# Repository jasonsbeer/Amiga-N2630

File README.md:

The N2630 is a 50MHz Motorolla MC68030 CPU card with additional RAM and ATA device port for the Amiga 2000 family of computers. It is installed in the CPU slot where it immediately upgrades the system to the MC68030 processor with FPU, up to 264 megabytes of Fast RAM, and an ATA port. The N2630 is intended to be an evolution of the A2630 card.  

<br />Look for the N2630 channel on Discord: https://discord.gg/NU7SPYfNFj  

## CURRENT STATUS:
**Revision 4.1.0a/b is the current production release.**  

Sub-revision "a" supports the PLCC footprint MC68882. Sub-revision "b" supports the PGA footprint MC68882. They are otherwise identical.  

See the [issues](https://github.com/jasonsbeer/Amiga-N2630/issues) tab for known issues. [Click here](/TestedDevices.md) to see a list of devices tested with the N2630.

## Features
1. Motorola 68030 microprocessor running at 50MHz.
2. Motorola 68882 math coprocessor running up to 50MHz.
3. 4 or 8 megabytes of Zorro 2 Fast RAM.
4. 16 to 256 megabytes of Zorro 3 Fast RAM.
5. ATA port with 40-pin cable and compact flash card options.

## Assembly Notes
Click [here](/AssemblyNotes.md) for more information on building the N2630.

## Installation Notes
This card may be installed in any Amiga 2000 computer. Installation is simply inserting the card into the 86 pin CPU/Coprocessor slot of the Amiga computer. There are no software drivers to install.  Kickstart v37.300 and greater is recommended.

**IMPORTANT:** Before installing a Revision 4.x.x or greater N2630, it is necessary to determine if you have an early, non-cost reduced motherboard. If your motherboard is marked "Made In Germany" and "(C) 1986 Commodore" on the left side of the board, you have a non-cost reduced Amiga 2000 board, designated "A2000" in this documentation. An example of a non-cost reduced Amiga 2000 motherboard can be see [here](http://amiga.resource.cx/photos/a2000,1). In the event you have an non-cost reduced "A2000" motherboard, you must remove the Motorola 68000 processor from the Amiga 2000 motherboard and place a jumper at J302 of the N2630.  All other Amiga 2000 motherboards are designated "B2000" and should leave the Motorola 68000 in place. Revision 3.0.x cards do not support the original German A2000. 

**NOTES:**  
**1) Hardware revision 4.x.x supports the original Germal A2000, but is untested.**  
**2) The A2091 hard drive card will not operate correctly when using Kickstart 1.x on a revision 6.2 or newer Amiga 2000 with the N2630 or A2630 CPU cards. You must use Kickstart 2.04 or newer.**

## 68030 Mode
By default, the N2630 starts in 68030 mode. When in 68030 mode, all installed RAM and the ATA device port are active.

## 68000 Mode
When desired, the 68030 may be disabled during a cold or warm start. This results in the Amiga falling back to the 68000 processor. This may be desired when software does not run correctly on the 68030 processor. To start up in 68000 mode, hold down the right mouse button during startup. Select "68000" and the Amiga will reset with the 68000 as the active processor. When in 68000 mode, the ATA port and on-board RAM are inactive. Motorola 68000 mode is not available with A2000 motherboards.

## 68882 Math Coprocessor (FPU)
The Motorolla MC68882 (or MC68881) floating point unit may be optionally added to the N2630. The FPU is typically driven at the same clock frequency as the MC68030 via the X1 oscillator, but may be clocked independently via the X2 oscillator (see Table 3, J202).

## ROMs
The N2630 requires two 27C256 EPROMs (burned by the user) to function. The ROMs handle the system startup for CPU selection and contains the [LIDE.device](https://github.com/LIV2/lide.device) AUTOBOOT ROM. See the instructions [here](/ROMs.md) for burning the N2630 ROMs.

## FAST RAM
The N2630 uses SDRAM to provide the necessary memory for the Amiga system. SDRAM is the successor to Fast Page Memory found in devices such as the Amiga 3000, A2630 processor card, and other computers of the time. SDRAMs are a cost effective way to supply memory to older systems and are readily available either new or from unused memory modules. 

### Zorro 2
Zorro 2 RAM is the Amiga RAM found in the 24 bit address space of the Motorola MC68000 processor. The Zorro 2 RAM on the N2630 is accessed by the 68030 as a 32-bit data bus and supports 16-bit DMA activities of the Zorro 2 bus. Placing a jumper at position J404 will limit the amount of RAM to 4MB in the Zorro 2 space, allowing 4MB of address space to be made available to other Zorro 2 devices. As an example, if you have a 4MB Zorro 2 video card, it will be necessary to set jumper J404 to free up this address space for the video card. Failure to do so will result in the video card failing to pass the AUTOCONFIG process. As another example, if you have two 4MB Zorro 2 devices, such as a video card and Bridge card, these devices require the entire 8MB Zorro 2 address space. In this situation, you must disable the Zorro 2 RAM entirely by placing a jumper at J403.

Using expansion memory on the Zorro 2 bus is not recommended, as this will negatively impact the performance of the MC68030 when accessing this memory on the Zorro 2 bus. The expansion memory on the N2630 should always be used as a first choice.

NOTE: Any SDRAM at least 2Mx16 in capacity in the 54-TSOP II footprint may be placed. However, it is not possible to achieve more than 8 megabytes of Zorro 2 RAM capacity. 

### Zorro 3
Zorro 3 RAM is the Amiga RAM found in the 32-bit address space of the Motorola MC68030 processor. The Zorro 3 RAM on the N2630 supports the cache burst mode of the 68030 processor. Both Zorro 2 and Zorro 3 RAM are used together on the N2630 card. Thus, the total memory available to the system will be the sum of the Zorro 2 and Zorro 3 RAM. 

Zorro 3 SDRAMs may be installed in different configurations to achieve a specific amount of final RAM (Table 1a). SDRAM must be installed in pairs, or banks, to achieve the needed 32 bit data path. Positions U406 and U407 represent the "low" bank and positions U408 and U409 represent the "high" bank. The banks must be populated as the low bank only or both low and high banks. The high bank will not function without the low bank populated. The SDRAM footprint is 54-TSOP II. The indicated jumpers must be set as shown or your system may not function correctly. When installing both banks, jumpers J400 and J401 must be set as shown in tables 1b and 1c. If only the low bank is populated, these jumpers are not used.

The Zorro 3 memory supports AUTOCONFIG with Kickstart 2.04 and newer and will be auto sized by Amiga OS. When using Kickstart version 1.x, place a jumper at J405 to disable the Zorro 3 AUTOCONFIG. An addmem style program may be used to add the Zorro 3 memory to the Amiga's memory pool. See Table 1d for the N2630 Zorro 3 memory map.

**Table 1a.** Possible Zorro 3 RAM Combinations for the N2630.
Desired Zorro</br>3 RAM (MB)|SDRAM|Low Bank</br>(U406 and U407)|High Bank</br>(U408 and U409)
-|-|-|-
16|4MX16|Populated<sup>A</sup>|Unpopulated<sup>B</sup>
32|4MX16|Populated|Populated
32|8MX16|Populated|Unpopulated
64|8MX16|Populated|Populated
64|16MX16|Populated|Unpopulated
128|16Mx16|Populated|Populated
128|32MX16|Populated|Unpopulated
256|32MX16|Populated|Populated

<sup>A</sup>These SDRAM positions are populated by the SDRAM indicated.  
<sup>B</sup>This SDRAM positions are not populated.

**Table 1b.** SDRAM Bank Jumper Setting.
Zorro 3 RAM</br>Banks Populated|J400
-|-
Low Bank Only|Open<sup>A</sup>
Both Banks|Shorted<sup>B</sup>

<sup>A</sup>No jumper.  
<sup>B</sup>Jumper placed. 
  
**Table 1c.** Jumper Configurations When Both Low and High Memory Banks Are Populated.
Desired Zorro</br>3 RAM (MB)|SDRAM</br>Capacity|J401<sup>[A]</sup>|J402<sup>[A]</sup>
-|-|-|-
32|4MX16|Open<sup>[B]</sup>|Shorted<sup>[C]</sup>
64|8MX16|Shorted|Open
128|16Mx16|Shorted|Shorted
256|32MX16|Open|Open

<sup>A</sup>Ignored when J400 is open.  
<sup>B</sup>No jumper.  
<sup>C</sup>Jumper placed.  

**Table 1d.** N2630 Zorro 3 Memory Map.
Desired Zorro</br>3 RAM (MB)|Starting Address|Ending Address
-|-|-
16|$40000000|$40FFFFFF
32|$40000000|$41FFFFFF
64|$40000000|$43FFFFFF
128|$40000000|$47FFFFFF
256|$40000000|$4FFFFFFF

## ATA Port
The N2630 includes a buffered, host terminated AUTOBOOT ATA port for hard drives and ATAPI devices. The N2630 implements [LIDE.device](https://github.com/LIV2/lide.device) as the ATA driver. The driver must be present on the N2630 ROMs for the ATA port to function. See [ROMs](#roms) for more details. The ATA port may be accessed via the 40-pin ATA header and the compact flash card slot. There are a few different ways to combine devices on the port, but the total number of ATA devices on the N2630 cannot exceed two (master and slave). For instructions on installing a new hard drive on Amiga computers, refer to the [Commodore Hard Drive User's Guide](DataSheet/Hard_Drive_Users_Guide.pdf). This includes the HDToolBox user guide and other useful information for setting up both ATA and SCSI devices. 

The ATA logic supports four speed modes: PIO0, PIO2, PIO4, and SanDisk Ultra 2 (see Table 2B). The modes PIO0, PIO2, and PIO4 follow the published timing specifications of those modes, with PIO0 being the slowest. The SanDisk Ultra 2 mode was developed for the SanDisk Ultra 2 compact flash card and is capable of 7.4M/s transfer rate. The SanDisk Ultra 2 mode is an undocumented ATA timing and may or may not work with other devices. The speed mode you select will be determined by the slowest ATA device on your system. To determine what speed your devices support, it is recommended to start with the slowest setting (PIO0) and adjust one setting faster until one of your devices stops working. The mode you choose should be the fastest mode where all devices function correctly. Jumpers should only be changed while the system is off.

Each ATA device must be set as slave or master. Devices present on the 40 pin ATA port may use cable select by shorting J905 when using a proper cable select ATA cable. See the manual for each device on how to designate the device's master or slave setting. Master and slave for the compact flash device are set via J901 on the N2630.

**NOTE:** The compact flash card slot is not affected by the cable select jumper (J905).  Thus, J905 should only be used when a proper cable select ATA cable is implemented on the 40 pin ATA port.

**Table 2A.** ATA Configuration Jumper Settings.
Jumper|Description|Open<sup>[A]</sup>|Shorted<sup>[B]</sup>
-|-|-|-
J900|RESERVED||
J901|Compact Flash Select|Slave|Master
J902|PIO MODE||
J903|PIO MODE||
J904|RESERVED||
J905|Cable Select|Disable|Enable

<sup>A</sup>No jumper.  
<sup>B</sup>Jumper placed. 

**Table 2B.** ATA PIO Mode.
Mode|J902|J903
-|-|-
PIO0|Shorted<sup>[A]</sup>|Shorted|
PIO2|Shorted|Open<sup>[B]</sup>|
PIO4|Open|Shorted|
SanDisk Ultra 2|Open|Open|

<sup>A</sup>Jumper placed.  
<sup>B</sup>No jumper.  

## Other Jumper Settings
In the following tables, OPEN indicates no jumper. Shorted indicates the presence of a jumper on the pins indicated. All jumpers must be set correctly or you may encounter unexpected behaviors or failure to boot.

**Table 3a.** Configuration Jumper Settings
Jumper|Description|Shorted|Open<sup>[A]</sup>
-|-|-|-
J302|Amiga Version|A2000|B2000
J304|OS Mode|Unix|Amiga OS
J403|Zorro 2 RAM|Disable|Enable
J404|Z2 4/8MB|4MB|8MB
J405|Zorro 3 RAM|Disable|Enable

<sup>A</sup>The factory configuration for all jumpers is open (no jumper).  

**Table 3b.** System Clock Jumper Settings
Jumper|Description|1-2|2-3
-|-|-|-
J202|FPU Clock|X1<sup>[A]</sup>|X2<sup>[B]</sup>

<sup>A</sup>FPU clock from X1. Factory default.  
<sup>B</sup>FPU clock from X2.

## Revision History
<strong>Revision 4.1.0a/b</strong>  
   Added ATA activity light buffer to address config issues with some ATA devices.  
   Changed polarity of the ATA LED header.  
   
<strong>Revision 4.0.1a/b</strong>  
   Sub-revision 'a' supports PLCC MC68882, sub-revision 'b' supports the PGA MC68882.  
   Changed jumper footprint to increase ease of assembly.  
   Added order number location for JLCPCB.  
   Added support for original German A2000 machines.
   
<strong>Revision 3.0.1</strong>  
   Added copper thieving areas to top and bottom layers.  
   
<strong>Revision 3.0</strong>  
   Initial production release.  

## Acknowledgements
Dave Haynie for sharing the A2630 technical details with the Amiga community.  
Matt Harlum (LIV2) for sharing his Gayle ATA code, LIDE.device, submitting code improvements, listening my struggles, and his numerous other contributions to this project.  
Stephen Durham (steveed) for loaning me his ethernet cards.  
Members of the Discord testing group: LIV2, steeveed, Chrissy, Pillock.  
Everyone who made the Amiga possible.  

Last Updated: March 26, 2024

## License
<br />This work is licensed under a <a rel="license" href="http://creativecommons.org/licenses/by-nc-sa/4.0/">Creative Commons Attribution-NonCommercial-ShareAlike 4.0 International License</a>.

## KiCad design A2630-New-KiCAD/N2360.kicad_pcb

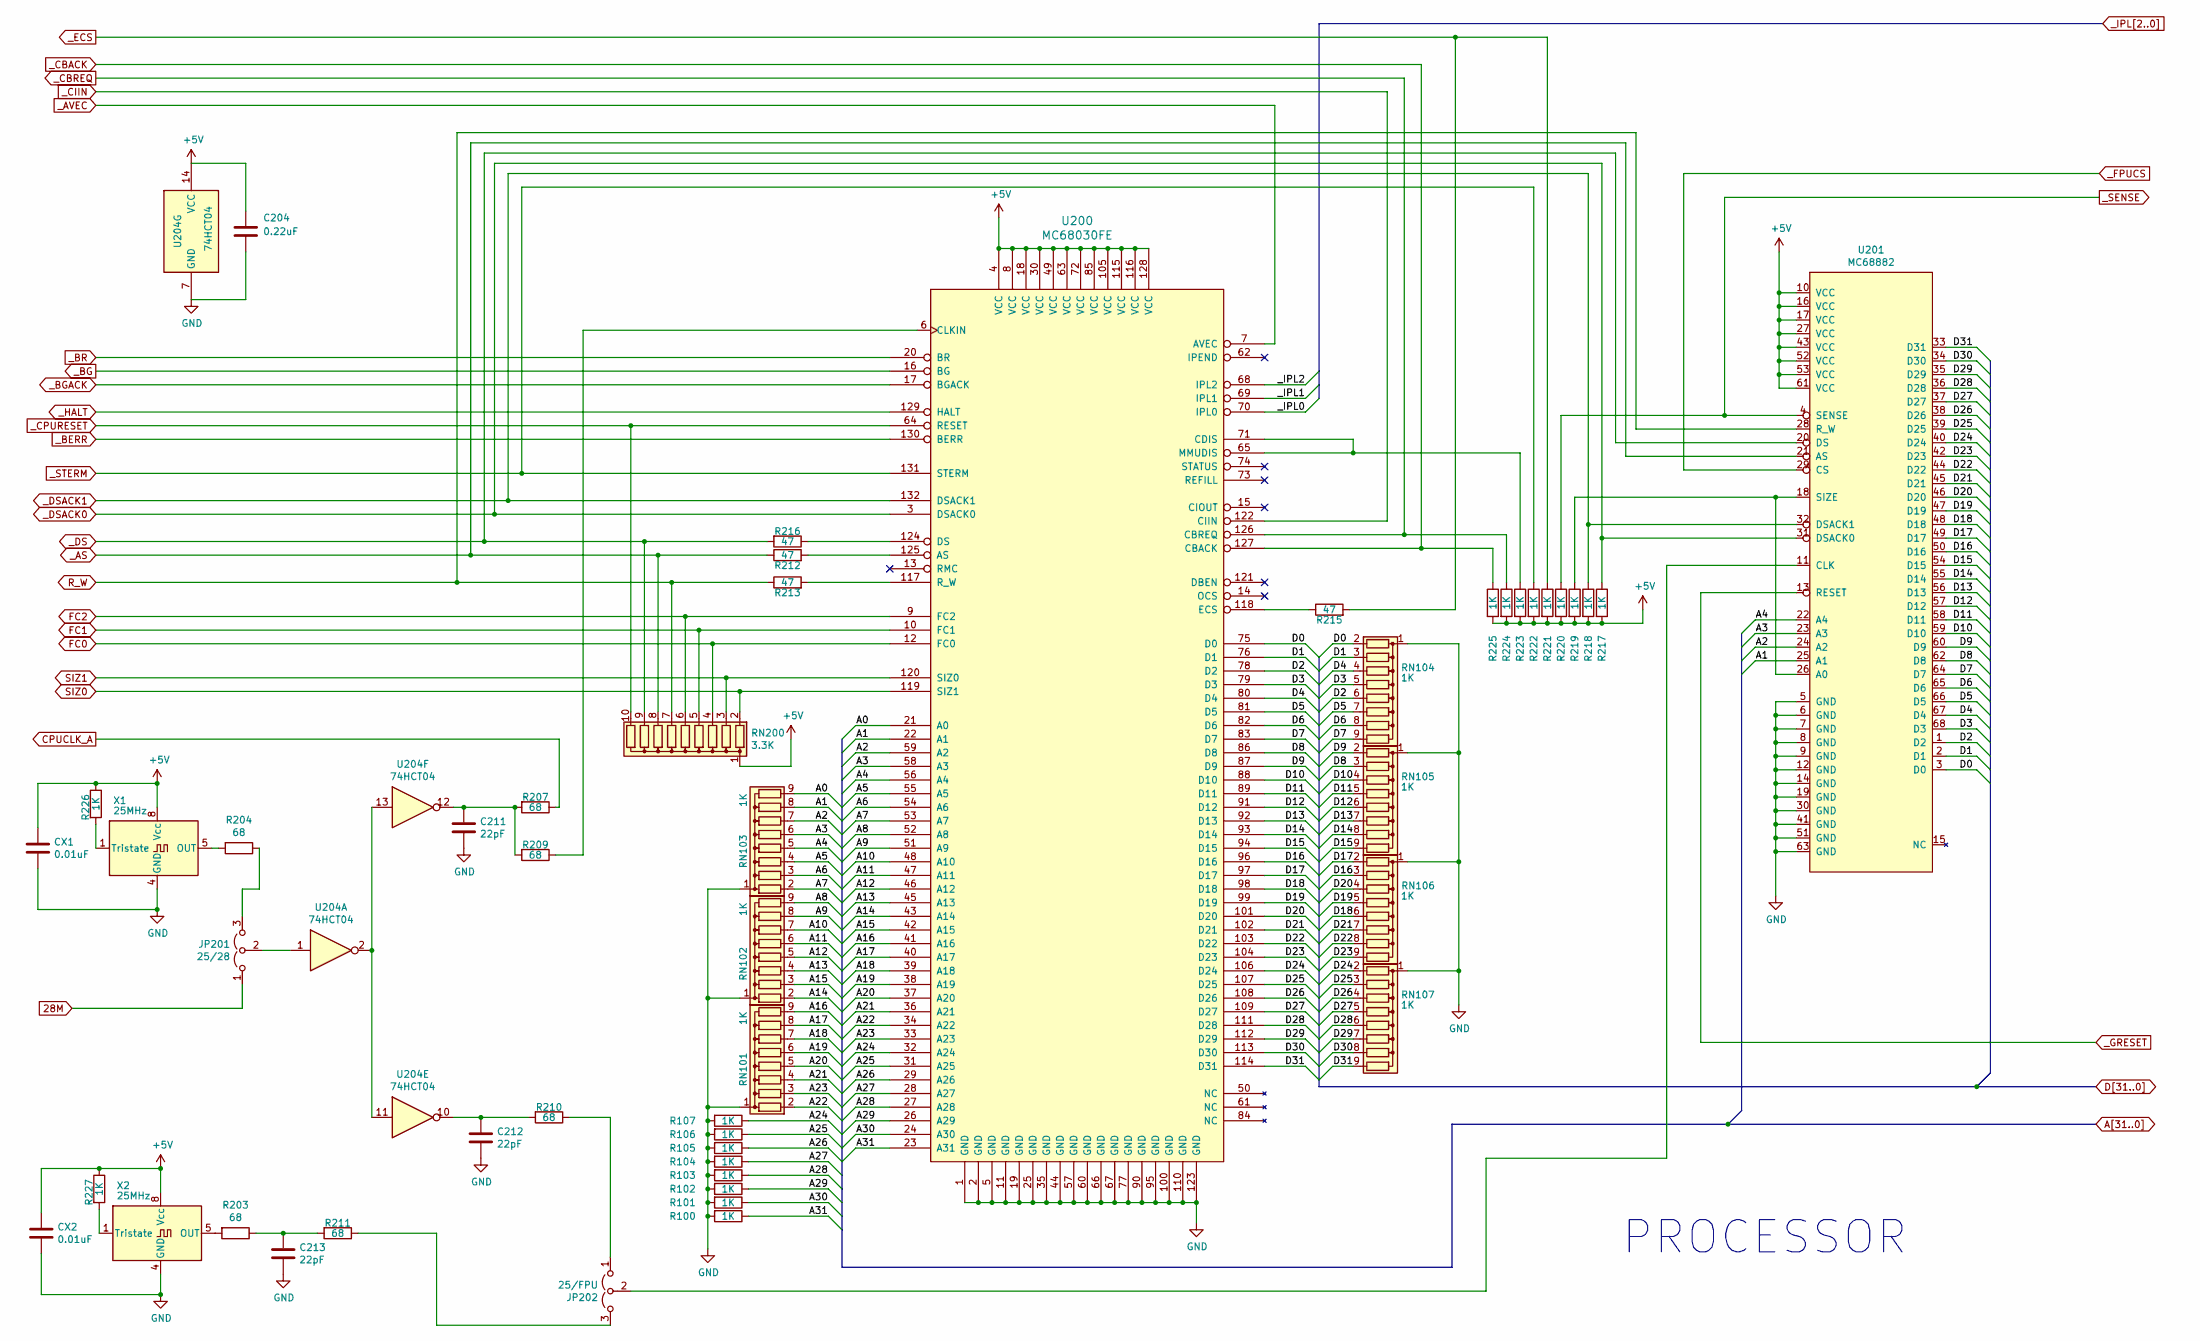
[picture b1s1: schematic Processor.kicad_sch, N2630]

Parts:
C204: 0.22uF; C_0805_2012Metric
C211, C212, C213: 22pF; C_0805_2012Metric
CX1, CX2: 0.01uF; C_0805_2012Metric
JP201: 25/28; PinHeader_1x03_P2.54mm_Vertical
JP202: 25/FPU; PinHeader_1x03_P2.54mm_Vertical
R100, R101, R102, R103, R104, R105, R106, R107, R217, R218, R219, R220, R221, R222, R223, R224, R225, R226, R227: 1K; R_0805_2012Metric
R203, R204, R207, R209, R210, R211: 68; R_0805_2012Metric
R212, R213, R215, R216: 47; R_0805_2012Metric
RN101, RN102, RN103, RN104, RN105, RN106, RN107: 1K; R_Array_SIP9
RN200: 3.3K; R_Array_SIP10; Digikey 4610X-1-332LF-ND
U200: MC68030FE; PQFP-132_24x24mm_P0.635mm
U201: MC68882; PLCC-68_THT-Socket
U204: 74HCT04; SOIC-14_3.9x8.7mm_P1.27mm; Digikey 296-31832-1-ND
X1, X2: 25MHz; Oscillator_DIP-8; Digikey 535-9175-5-ND

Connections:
28M: JP201.1 (A); also elsewhere on the board
A0: RN103.9 (R8), U200.21 (A0); also elsewhere on the board
A1: RN103.8 (R7), U200.22 (A1), U201.25 (A1); also elsewhere on the board
A2: RN103.7 (R6), U200.59 (A2), U201.24 (A2); also elsewhere on the board
A3: RN103.6 (R5), U200.58 (A3), U201.23 (A3); also elsewhere on the board
A4: RN103.5 (R4), U200.56 (A4), U201.22 (A4); also elsewhere on the board
A5: RN103.4 (R3), U200.55 (A5); also elsewhere on the board
A6: RN103.3 (R2), U200.54 (A6); also elsewhere on the board
A7: RN103.2 (R1), U200.53 (A7); also elsewhere on the board
A8: RN102.9 (R8), U200.52 (A8); also elsewhere on the board
A9: RN102.8 (R7), U200.51 (A9); also elsewhere on the board
A10: RN102.7 (R6), U200.48 (A10); also elsewhere on the board
A11: RN102.6 (R5), U200.47 (A11); also elsewhere on the board
A12: RN102.5 (R4), U200.46 (A12); also elsewhere on the board
A13: RN102.4 (R3), U200.45 (A13); also elsewhere on the board
A14: RN102.2 (R1), U200.43 (A14); also elsewhere on the board
A15: RN102.3 (R2), U200.42 (A15); also elsewhere on the board
A16: RN101.9 (R8), U200.41 (A16); also elsewhere on the board
A17: RN101.8 (R7), U200.40 (A17); also elsewhere on the board
A18: RN101.7 (R6), U200.39 (A18); also elsewhere on the board
A19: RN101.6 (R5), U200.38 (A19); also elsewhere on the board
A20: RN101.5 (R4), U200.37 (A20); also elsewhere on the board
A21: RN101.4 (R3), U200.36 (A21); also elsewhere on the board
A22: RN101.2 (R1), U200.34 (A22); also elsewhere on the board
A23: RN101.3 (R2), U200.33 (A23); also elsewhere on the board
A24: R107.1, U200.32 (A24); also elsewhere on the board
A25: R106.1, U200.31 (A25); also elsewhere on the board
A26: R105.1, U200.29 (A26); also elsewhere on the board
A27: R104.1, U200.28 (A27)
A28: R103.1, U200.27 (A28)
A29: R102.1, U200.26 (A29)
A30: R101.1, U200.24 (A30)
A31: R100.1, U200.23 (A31)
CPUCLK_A: R207.1; also elsewhere on the board
D0: RN104.2 (R1), U200.75 (D0), U201.3 (D0); also elsewhere on the board
D1: RN104.3 (R2), U200.76 (D1), U201.2 (D1); also elsewhere on the board
D2: RN104.6 (R5), U200.78 (D2), U201.1 (D2); also elsewhere on the board
D3: RN104.5 (R4), U200.79 (D3), U201.68 (D3); also elsewhere on the board
D4: RN104.4 (R3), U200.80 (D4), U201.67 (D4); also elsewhere on the board
D5: RN104.7 (R6), U200.81 (D5), U201.66 (D5); also elsewhere on the board
D6: RN104.8 (R7), U200.82 (D6), U201.65 (D6); also elsewhere on the board
D7: RN104.9 (R8), U200.83 (D7), U201.64 (D7); also elsewhere on the board
D8: RN105.3 (R2), U200.86 (D8), U201.62 (D8); also elsewhere on the board
D9: RN105.2 (R1), U200.87 (D9), U201.60 (D9); also elsewhere on the board
D10: RN105.4 (R3), U200.88 (D10), U201.59 (D10); also elsewhere on the board
D11: RN105.5 (R4), U200.89 (D11), U201.58 (D11); also elsewhere on the board
D12: RN105.6 (R5), U200.91 (D12), U201.57 (D12); also elsewhere on the board
D13: RN105.7 (R6), U200.92 (D13), U201.56 (D13); also elsewhere on the board
D14: RN105.8 (R7), U200.93 (D14), U201.55 (D14); also elsewhere on the board
D15: RN105.9 (R8), U200.94 (D15), U201.54 (D15); also elsewhere on the board
D16: RN106.3 (R2), U200.96 (D16), U201.50 (D16); also elsewhere on the board
D17: RN106.2 (R1), U200.97 (D17), U201.49 (D17); also elsewhere on the board
D18: RN106.6 (R5), U200.98 (D18), U201.48 (D18); also elsewhere on the board
D19: RN106.5 (R4), U200.99 (D19), U201.47 (D19); also elsewhere on the board
D20: RN106.4 (R3), U200.101 (D20), U201.46 (D20); also elsewhere on the board
D21: RN106.7 (R6), U200.102 (D21), U201.45 (D21); also elsewhere on the board
D22: RN106.8 (R7), U200.103 (D22), U201.44 (D22); also elsewhere on the board
D23: RN106.9 (R8), U200.104 (D23), U201.42 (D23); also elsewhere on the board
D24: RN107.2 (R1), U200.106 (D24), U201.40 (D24); also elsewhere on the board
D25: RN107.3 (R2), U200.107 (D25), U201.39 (D25); also elsewhere on the board
D26: RN107.4 (R3), U200.108 (D26), U201.38 (D26); also elsewhere on the board
D27: RN107.5 (R4), U200.109 (D27), U201.37 (D27); also elsewhere on the board
D28: RN107.6 (R5), U200.111 (D28), U201.36 (D28); also elsewhere on the board
D29: RN107.7 (R6), U200.112 (D29), U201.35 (D29); also elsewhere on the board
D30: RN107.8 (R7), U200.113 (D30), U201.34 (D30); also elsewhere on the board
D31: RN107.9 (R8), U200.114 (D31), U201.33 (D31); also elsewhere on the board
FC0: RN200.4 (R3), U200.12 (FC0); also elsewhere on the board
FC1: RN200.5 (R4), U200.10 (FC1); also elsewhere on the board
FC2: RN200.6 (R5), U200.9 (FC2); also elsewhere on the board
unnamed: C211.1, R207.2, R209.2, U204.12
unnamed: C212.1, R210.2, U204.10
unnamed: C213.1, R203.1, R211.2
unnamed: JP201.2 (C), U204.1
unnamed: JP201.3 (B), R204.1
unnamed: JP202.1 (A), R210.1
unnamed: JP202.2 (C), U201.11 (CLK)
unnamed: JP202.3 (B), R211.1
unnamed: R203.2, X2.5 (OUT)
unnamed: R204.2, X1.5 (OUT)
unnamed: R209.1, U200.6 (CLKIN)
unnamed: R212.2, U200.125 (AS)
unnamed: R213.2, U200.117 (R_W)
unnamed: R215.1, U200.118 (ECS)
unnamed: R216.1, U200.124 (DS)
unnamed: R219.1, U201.18 (SIZE), U201.26 (A0)
unnamed: R223.1, U200.65 (MMUDIS), U200.71 (CDIS)
unnamed: R226.2, X1.1 (Tristate)
unnamed: R227.2, X2.1 (Tristate)
unnamed: U204.2, U204.11, U204.13
R_W: R213.1, RN200.7 (R6), U201.28 (R_W); also elsewhere on the board
SIZ0: RN200.2 (R1), U200.119 (SIZ1); also elsewhere on the board
SIZ1: RN200.3 (R2), U200.120 (SIZ0); also elsewhere on the board
_AS: R212.1, RN200.8 (R7), U201.21 (AS); also elsewhere on the board
_AVEC: U200.7 (AVEC); also elsewhere on the board
_BERR: U200.130 (BERR); also elsewhere on the board
_BG: U200.16 (BG); also elsewhere on the board
_BGACK: U200.17 (BGACK); also elsewhere on the board
_BR: U200.20 (BR)
_CBACK: R225.1, U200.127 (CBACK); also elsewhere on the board
_CBREQ: R224.1, U200.126 (CBREQ); also elsewhere on the board
_CIIN: U200.122 (CIIN); also elsewhere on the board
_CPURESET: RN200.10 (R9), U200.64 (RESET); also elsewhere on the board
_DS: R216.2, RN200.9 (R8), U201.20 (DS); also elsewhere on the board
_DSACK0: R217.1, U200.3 (DSACK0), U201.31 (DSACK0); also elsewhere on the board
_DSACK1: R218.1, U200.132 (DSACK1), U201.32 (DSACK1); also elsewhere on the board
_ECS: R215.2, R221.1
_FPUCS: U201.29 (CS); also elsewhere on the board
_GRESET: U201.13 (RESET); also elsewhere on the board
_HALT: U200.129 (HALT); also elsewhere on the board
_IPL0: U200.70 (IPL0); also elsewhere on the board
_IPL1: U200.69 (IPL1); also elsewhere on the board
_IPL2: U200.68 (IPL2); also elsewhere on the board
_SENSE: R220.1, U201.4 (SENSE); also elsewhere on the board
_STERM: R222.1, U200.131 (STERM); also elsewhere on the board

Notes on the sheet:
PROCESSOR

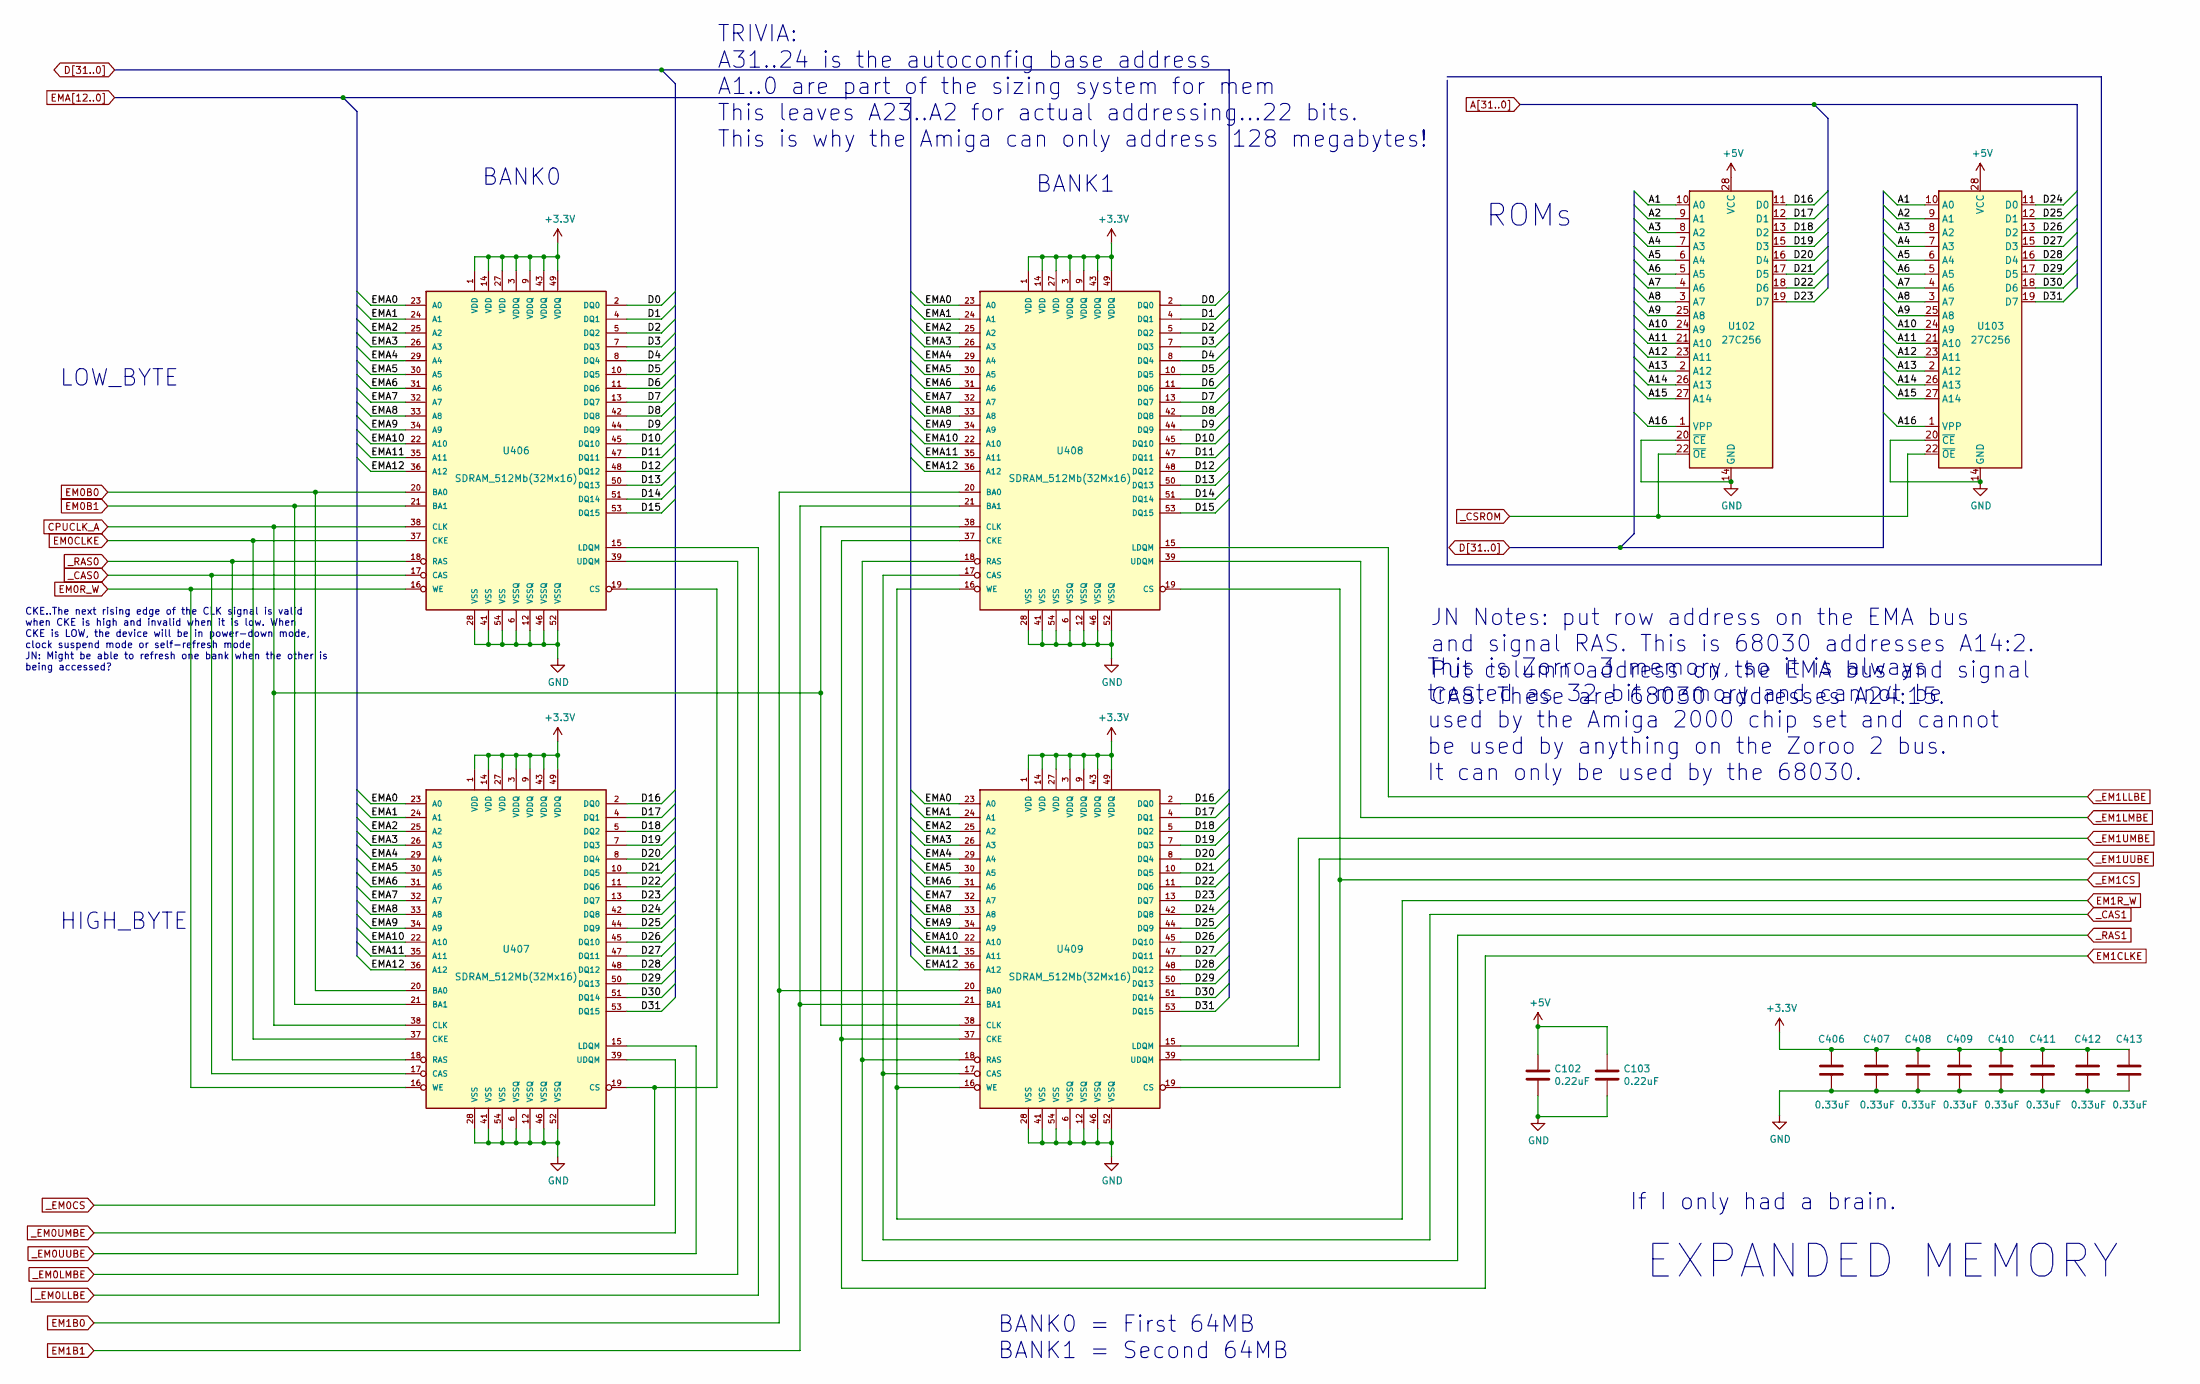
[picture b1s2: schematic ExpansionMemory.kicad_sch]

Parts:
C102, C103: 0.22uF; C_0805_2012Metric
C406, C407, C408, C409, C410, C411, C412, C413: 0.33uF; C_0805_2012Metric
U102, U103: 27C256; DIP-28_W15.24mm
U406, U407, U408, U409: SDRAM_512Mb(32Mx16); TSOP-II-54_22.2x10.16mm_P0.8mm

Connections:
+3V3: C406.1, C407.1, C408.1, C409.1, C410.1, C411.1, C412.1, C413.1, U406.1 (VDD), U406.3 (VDDQ), U406.9 (VDDQ), U406.14 (VDD), U406.27 (VDD), U406.43 (VDDQ), U406.49 (VDDQ), U407.1 (VDD), U407.3 (VDDQ), U407.9 (VDDQ), U407.14 (VDD), U407.27 (VDD), U407.43 (VDDQ), U407.49 (VDDQ), U408.1 (VDD), U408.3 (VDDQ), U408.9 (VDDQ), U408.14 (VDD), U408.27 (VDD), U408.43 (VDDQ), U408.49 (VDDQ), U409.1 (VDD), U409.3 (VDDQ), U409.9 (VDDQ), U409.14 (VDD), U409.27 (VDD), U409.43 (VDDQ), U409.49 (VDDQ); also elsewhere on the board
A1: U102.10 (A0), U103.10 (A0); also elsewhere on the board
A2: U102.9 (A1), U103.9 (A1); also elsewhere on the board
A3: U102.8 (A2), U103.8 (A2); also elsewhere on the board
A4: U102.7 (A3), U103.7 (A3); also elsewhere on the board
A5: U102.6 (A4), U103.6 (A4); also elsewhere on the board
A6: U102.5 (A5), U103.5 (A5); also elsewhere on the board
A7: U102.4 (A6), U103.4 (A6); also elsewhere on the board
A8: U102.3 (A7), U103.3 (A7); also elsewhere on the board
A9: U102.25 (A8), U103.25 (A8); also elsewhere on the board
A10: U102.24 (A9), U103.24 (A9); also elsewhere on the board
A11: U102.21 (A10), U103.21 (A10); also elsewhere on the board
A12: U102.23 (A11), U103.23 (A11); also elsewhere on the board
A13: U102.2 (A12), U103.2 (A12); also elsewhere on the board
A14: U102.26 (A13), U103.26 (A13); also elsewhere on the board
A15: U102.27 (A14), U103.27 (A14); also elsewhere on the board
A16: U102.1 (VPP), U103.1 (VPP); also elsewhere on the board
CPUCLK_A: U406.38 (CLK), U407.38 (CLK), U408.38 (CLK), U409.38 (CLK); also elsewhere on the board
D0: U406.2 (DQ0), U408.2 (DQ0); also elsewhere on the board
D1: U406.4 (DQ1), U408.4 (DQ1); also elsewhere on the board
D2: U406.5 (DQ2), U408.5 (DQ2); also elsewhere on the board
D3: U406.7 (DQ3), U408.7 (DQ3); also elsewhere on the board
D4: U406.8 (DQ4), U408.8 (DQ4); also elsewhere on the board
D5: U406.10 (DQ5), U408.10 (DQ5); also elsewhere on the board
D6: U406.11 (DQ6), U408.11 (DQ6); also elsewhere on the board
D7: U406.13 (DQ7), U408.13 (DQ7); also elsewhere on the board
D8: U406.42 (DQ8), U408.42 (DQ8); also elsewhere on the board
D9: U406.44 (DQ9), U408.44 (DQ9); also elsewhere on the board
D10: U406.45 (DQ10), U408.45 (DQ10); also elsewhere on the board
D11: U406.47 (DQ11), U408.47 (DQ11); also elsewhere on the board
D12: U406.48 (DQ12), U408.48 (DQ12); also elsewhere on the board
D13: U406.50 (DQ13), U408.50 (DQ13); also elsewhere on the board
D14: U406.51 (DQ14), U408.51 (DQ14); also elsewhere on the board
D15: U406.53 (DQ15), U408.53 (DQ15); also elsewhere on the board
D16: U102.11 (D0), U407.2 (DQ0), U409.2 (DQ0); also elsewhere on the board
D17: U102.12 (D1), U407.4 (DQ1), U409.4 (DQ1); also elsewhere on the board
D18: U102.13 (D2), U407.5 (DQ2), U409.5 (DQ2); also elsewhere on the board
D19: U102.15 (D3), U407.7 (DQ3), U409.7 (DQ3); also elsewhere on the board
D20: U102.16 (D4), U407.8 (DQ4), U409.8 (DQ4); also elsewhere on the board
D21: U102.17 (D5), U407.10 (DQ5), U409.10 (DQ5); also elsewhere on the board
D22: U102.18 (D6), U407.11 (DQ6), U409.11 (DQ6); also elsewhere on the board
D23: U102.19 (D7), U407.13 (DQ7), U409.13 (DQ7); also elsewhere on the board
D24: U103.11 (D0), U407.42 (DQ8), U409.42 (DQ8); also elsewhere on the board
D25: U103.12 (D1), U407.44 (DQ9), U409.44 (DQ9); also elsewhere on the board
D26: U103.13 (D2), U407.45 (DQ10), U409.45 (DQ10); also elsewhere on the board
D27: U103.15 (D3), U407.47 (DQ11), U409.47 (DQ11); also elsewhere on the board
D28: U103.16 (D4), U407.48 (DQ12), U409.48 (DQ12); also elsewhere on the board
D29: U103.17 (D5), U407.50 (DQ13), U409.50 (DQ13); also elsewhere on the board
D30: U103.18 (D6), U407.51 (DQ14), U409.51 (DQ14); also elsewhere on the board
D31: U103.19 (D7), U407.53 (DQ15), U409.53 (DQ15); also elsewhere on the board
EM0B0: U406.20 (BA0), U407.20 (BA0); also elsewhere on the board
EM0B1: U406.21 (BA1), U407.21 (BA1); also elsewhere on the board
EM0CLKE: U406.37 (CKE), U407.37 (CKE); also elsewhere on the board
EM0R_W: U406.16 (WE), U407.16 (WE); also elsewhere on the board
EM1B0: U408.20 (BA0), U409.20 (BA0); also elsewhere on the board
EM1B1: U408.21 (BA1), U409.21 (BA1); also elsewhere on the board
EM1CLKE: U408.37 (CKE), U409.37 (CKE); also elsewhere on the board
EM1R_W: U408.16 (WE), U409.16 (WE); also elsewhere on the board
EMA0: U406.23 (A0), U407.23 (A0), U408.23 (A0), U409.23 (A0); also elsewhere on the board
EMA1: U406.24 (A1), U407.24 (A1), U408.24 (A1), U409.24 (A1); also elsewhere on the board
EMA2: U406.25 (A2), U407.25 (A2), U408.25 (A2), U409.25 (A2); also elsewhere on the board
EMA3: U406.26 (A3), U407.26 (A3), U408.26 (A3), U409.26 (A3); also elsewhere on the board
EMA4: U406.29 (A4), U407.29 (A4), U408.29 (A4), U409.29 (A4); also elsewhere on the board
EMA5: U406.30 (A5), U407.30 (A5), U408.30 (A5), U409.30 (A5); also elsewhere on the board
EMA6: U406.31 (A6), U407.31 (A6), U408.31 (A6), U409.31 (A6); also elsewhere on the board
EMA7: U406.32 (A7), U407.32 (A7), U408.32 (A7), U409.32 (A7); also elsewhere on the board
EMA8: U406.33 (A8), U407.33 (A8), U408.33 (A8), U409.33 (A8); also elsewhere on the board
EMA9: U406.34 (A9), U407.34 (A9), U408.34 (A9), U409.34 (A9); also elsewhere on the board
EMA10: U406.22 (A10), U407.22 (A10), U408.22 (A10), U409.22 (A10); also elsewhere on the board
EMA11: U406.35 (A11), U407.35 (A11), U408.35 (A11), U409.35 (A11); also elsewhere on the board
EMA12: U406.36 (A12), U407.36 (A12), U408.36 (A12), U409.36 (A12); also elsewhere on the board
_CAS0: U406.17 (CAS), U407.17 (CAS); also elsewhere on the board
_CAS1: U408.17 (CAS), U409.17 (CAS); also elsewhere on the board
_CSROM: U102.22 (~OE), U103.22 (~OE); also elsewhere on the board
_EM0CS: U406.19 (CS), U407.19 (CS)
_EM0LLBE: U406.15 (LDQM); also elsewhere on the board
_EM0LMBE: U406.39 (UDQM); also elsewhere on the board
_EM0UMBE: U407.39 (UDQM); also elsewhere on the board
_EM0UUBE: U407.15 (LDQM); also elsewhere on the board
_EM1CS: U408.19 (CS), U409.19 (CS)
_EM1LLBE: U408.15 (LDQM); also elsewhere on the board
_EM1LMBE: U408.39 (UDQM); also elsewhere on the board
_EM1UMBE: U409.15 (LDQM); also elsewhere on the board
_EM1UUBE: U409.39 (UDQM); also elsewhere on the board
_RAS0: U406.18 (RAS), U407.18 (RAS); also elsewhere on the board
_RAS1: U408.18 (RAS), U409.18 (RAS); also elsewhere on the board

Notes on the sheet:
EXPANDED MEMORY
This is Zorro 3 memory, so it is always treated as 32 bit memory and cannot be used by the Amiga 2000 chip set and cannot be used by anything on the Zoroo 2 bus. It can only be used by the 68030.
LOW_BYTE
CKE..The next rising edge of the CLK signal is valid when CKE is high and invalid when it is low. When CKE is LOW, the device will be in power-down mode, clock suspend mode or self-refresh mode JN: Might be able to refresh one bank when the other is being accessed?
BANK1
BANK0
BANK0 = First 64MB BANK1 = Second 64MB
If I only had a brain.
ROMs
TRIVIA: A31..24 is the autoconfig base address A1..0 are part of the sizing system for mem This leaves A23..A2 for actual addressing...22 bits. This is why the Amiga can only address 128 megabytes!
JN Notes: put row address on the EMA bus and signal RAS. This is 68030 addresses A14:2. Put column address on the EMA bus and signal CAS. These are 68030 addresses A24:15.
HIGH_BYTE
